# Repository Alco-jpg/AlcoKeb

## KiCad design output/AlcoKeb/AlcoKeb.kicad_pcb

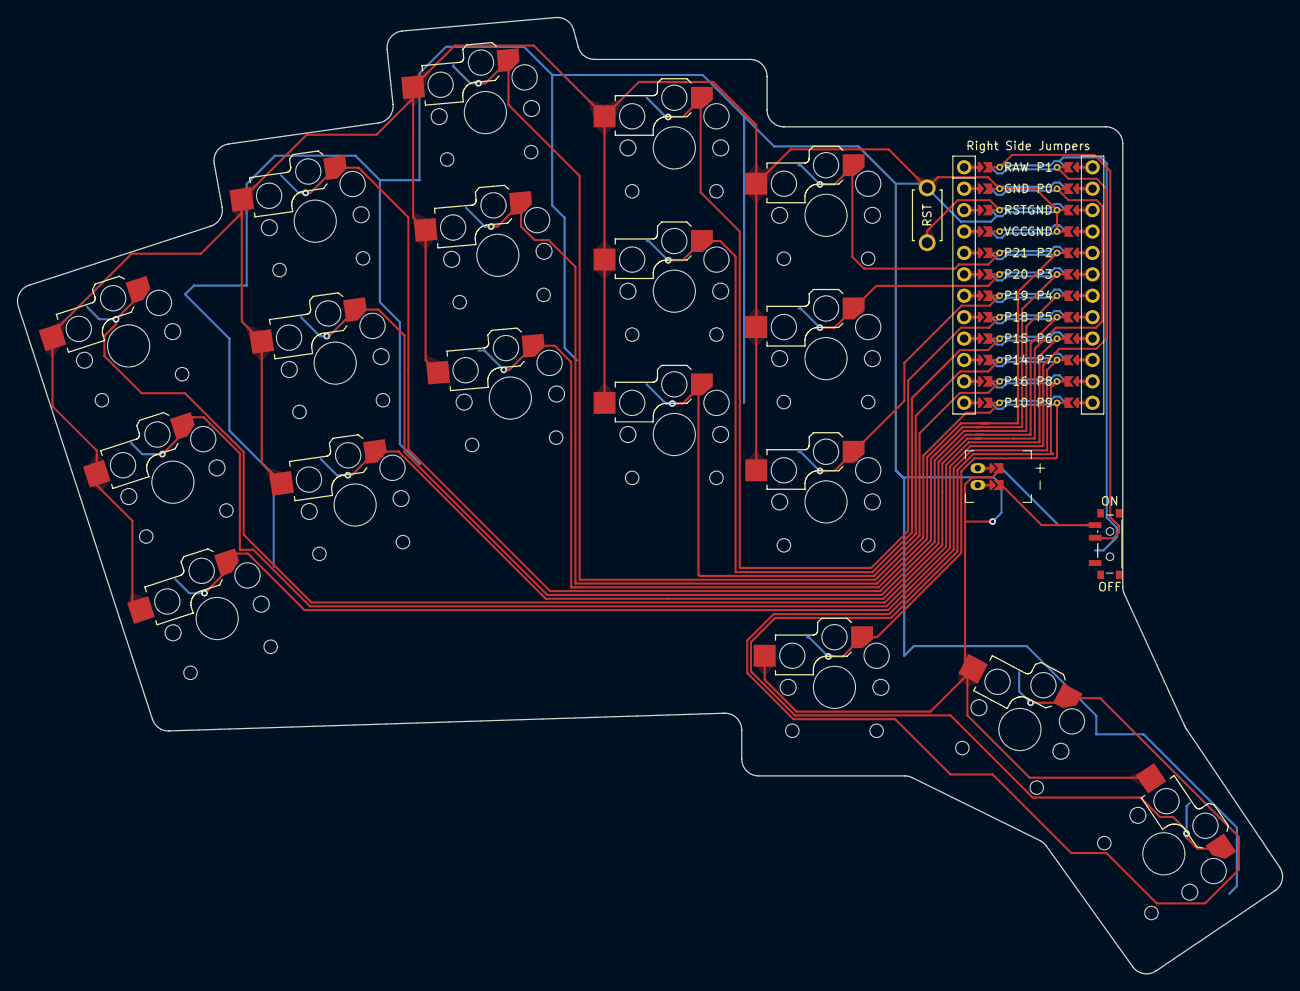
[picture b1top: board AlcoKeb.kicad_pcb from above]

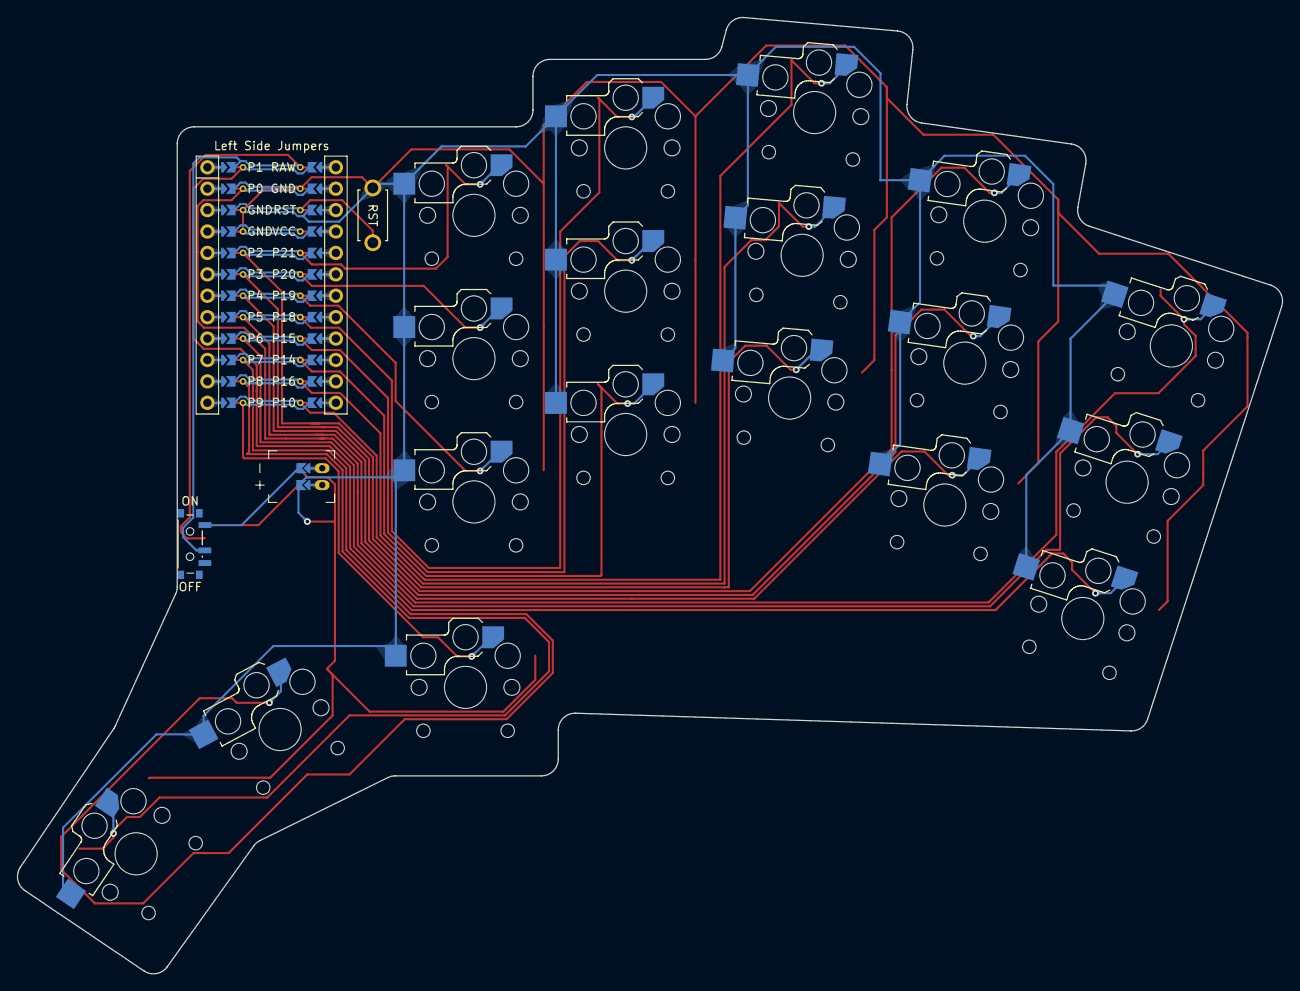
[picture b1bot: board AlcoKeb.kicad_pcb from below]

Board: 2 copper layers, 150.1 x 113.5 mm, 22 parts (18 on the bottom side), 24 nets.

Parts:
JST1: battery_connector_jst_ph_2
MCU1: mcu_nice_nano
PWR1: power_switch; power_switch_smd_side
RST1: reset_switch_tht_top
S1, S2, S3, S4, S5, S6, S7, S8, S9, S10, S11, S12, S13, S14, S15, S16, S17, S18: switch_choc_v1_v2

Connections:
BAT_P: JST1.1, PWR1.1, PWR1.3
GND: JST1.2, MCU1.3, MCU1.4, MCU1.123, RST1.2, S1.2, S2.2, S3.2, S4.2, S5.2, S6.2, S7.2, S8.2, S9.2, S10.2, S11.2, S12.2, S13.2, S14.2, S15.2, S16.2, S17.2, S18.2
JST1_1: JST1.11, JST1.21, JST1.31
JST1_2: JST1.12, JST1.22, JST1.32
P0: MCU1.2, S3.1
P1: MCU1.1, S1.1
P2: MCU1.5, S7.1
P3: MCU1.6, S6.1
P4: MCU1.7, S5.1
P5: MCU1.8, S4.1
P6: MCU1.9, S2.1
P7: MCU1.10, S17.1
P8: MCU1.11, S18.1
P9: MCU1.12, S16.1
P10: MCU1.113, S8.1
P14: MCU1.115, S10.1
P15: MCU1.116, S11.1
P16: MCU1.114, S9.1
P18: MCU1.117, S12.1
P19: MCU1.118, S13.1
P20: MCU1.119, S14.1
P21: MCU1.120, S15.1
RAW: MCU1.124, PWR1.2
RST: MCU1.122, RST1.1

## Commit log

2024-04-15 Changed layout
2024-04-15 Added board constraints and fixed minor things
2024-04-15 Small fixes
